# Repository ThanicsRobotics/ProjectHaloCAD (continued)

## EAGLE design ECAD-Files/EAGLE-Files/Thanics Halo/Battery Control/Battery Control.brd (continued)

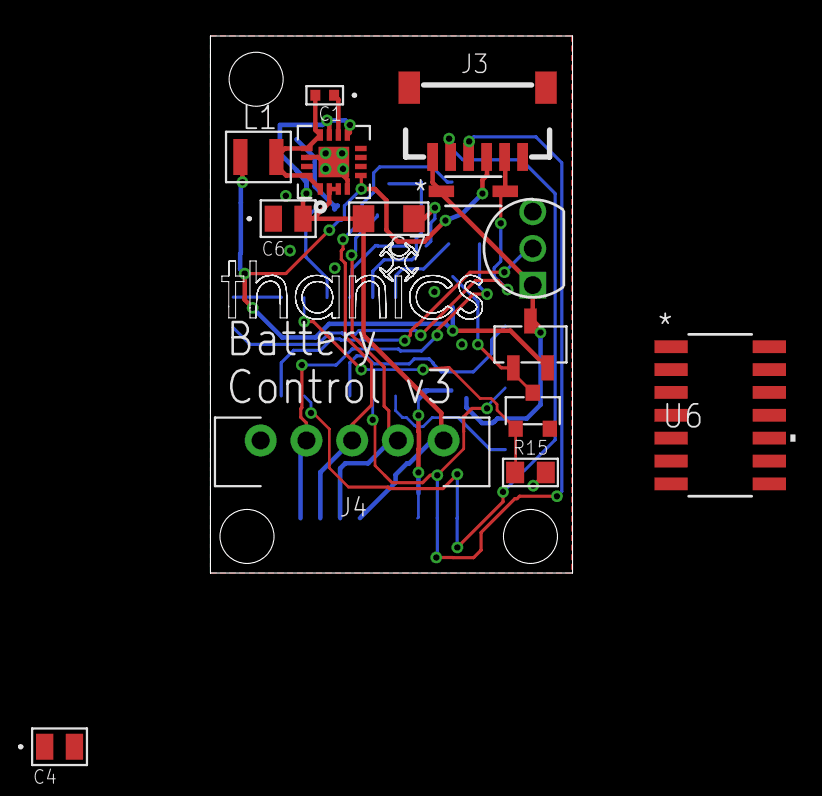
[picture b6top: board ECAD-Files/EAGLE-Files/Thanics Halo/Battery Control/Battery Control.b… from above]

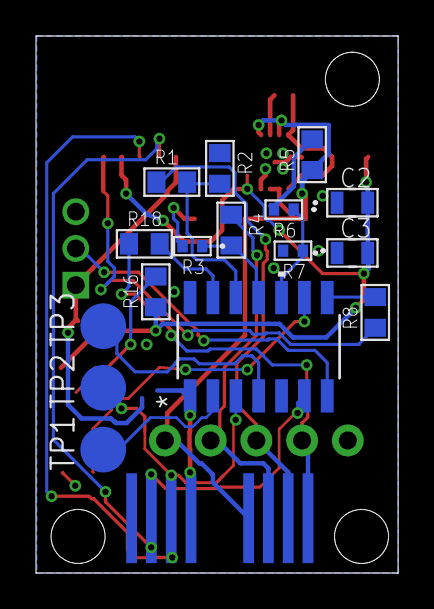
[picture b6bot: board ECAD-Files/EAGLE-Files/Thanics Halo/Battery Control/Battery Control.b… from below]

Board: 2 copper layers, 20.1 x 29.8 mm, 31 parts (17 on the bottom side), 23 nets.

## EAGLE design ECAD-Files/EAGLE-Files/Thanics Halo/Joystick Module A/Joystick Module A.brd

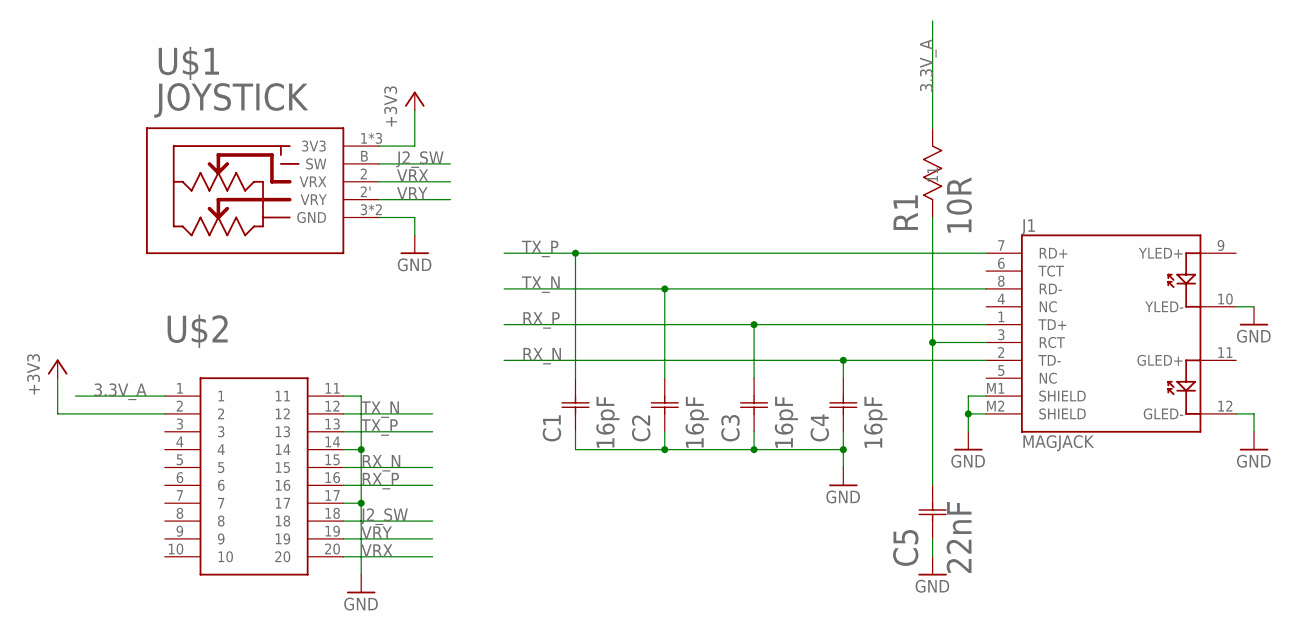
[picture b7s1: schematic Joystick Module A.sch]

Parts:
C1, C2, C3, C4: 16pF; G-155-M
C5: 22nF; G-155-M
J1: MAGJACK
R1: 10R; STA_RNCP0805-M
U$1: JOYSTICK"; JOYSTICK
U$2: EDGE_CONNECTOR_20POS_CONTACTS

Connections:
3.3V_A: R1.2 (22), U$2.1
+3V3: U$1.1 (3V3), U$1.1' (3V3), U$1.A (3V3), U$2.2
GND: C1.1 (11), C2.1 (11), C3.1 (11), C4.1 (11), C5.1 (11), J1.10 (YLED-), J1.12 (GLED-), J1.M1 (SHIELD), J1.M2 (SHIELD), U$1.3 (GND), U$1.3' (GND), U$2.11, U$2.14, U$2.17
J2_SW: U$1.B (SW), U$2.18
unnamed: C5.2 (22), J1.3 (RCT), R1.1 (11)
RX_N: C4.2 (22), J1.2 (TD-), U$2.15
RX_P: C3.2 (22), J1.1 (TD+), U$2.16
TX_N: C2.2 (22), J1.8 (RD-), U$2.12
TX_P: C1.2 (22), J1.7 (RD+), U$2.13
VRX: U$1.2 (VRX), U$2.20
VRY: U$1.2' (VRY), U$2.19

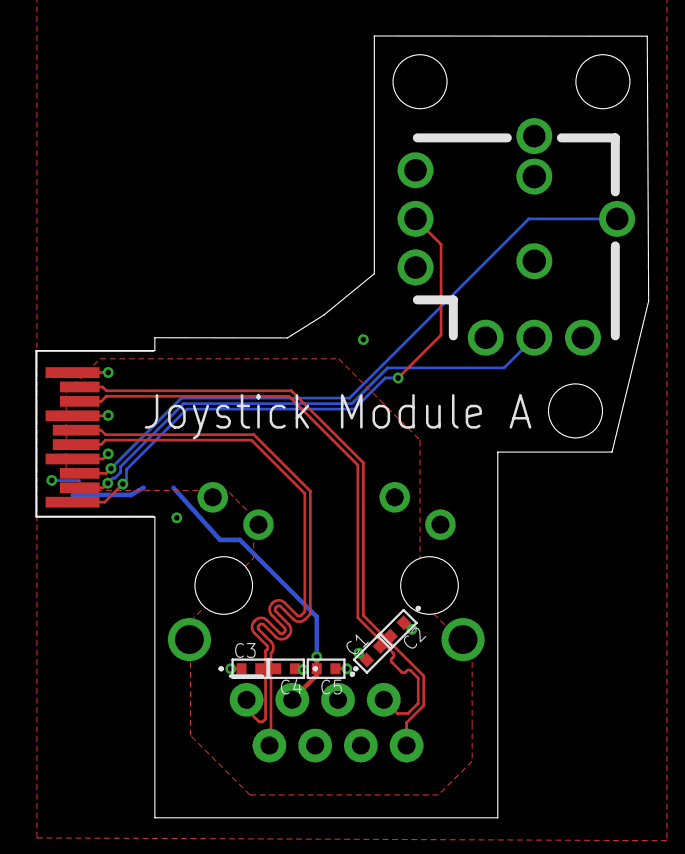
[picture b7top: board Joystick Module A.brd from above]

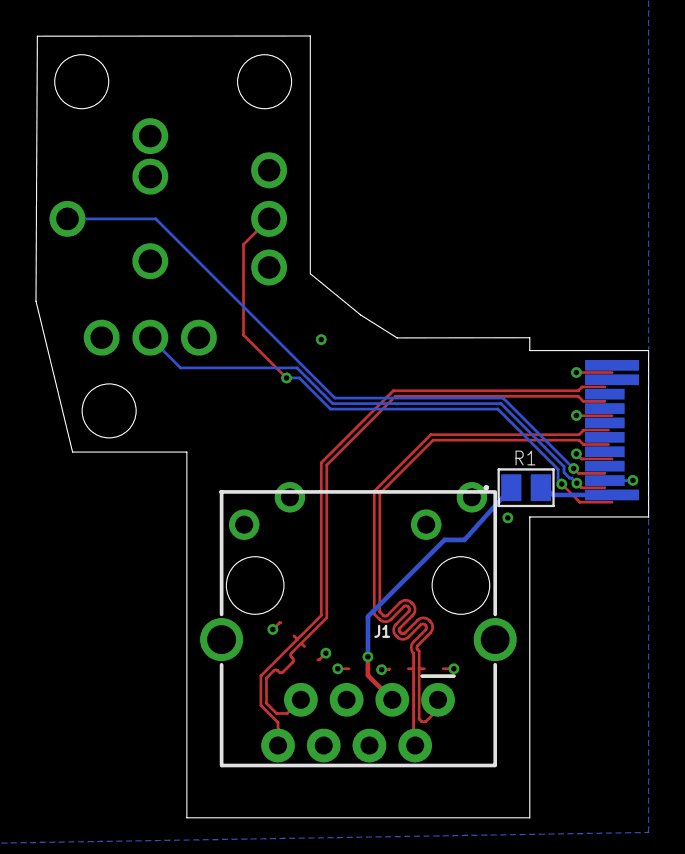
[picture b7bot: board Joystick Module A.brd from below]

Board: 4 copper layers, 34.0 x 43.4 mm, 9 parts (2 on the bottom side), 11 nets.

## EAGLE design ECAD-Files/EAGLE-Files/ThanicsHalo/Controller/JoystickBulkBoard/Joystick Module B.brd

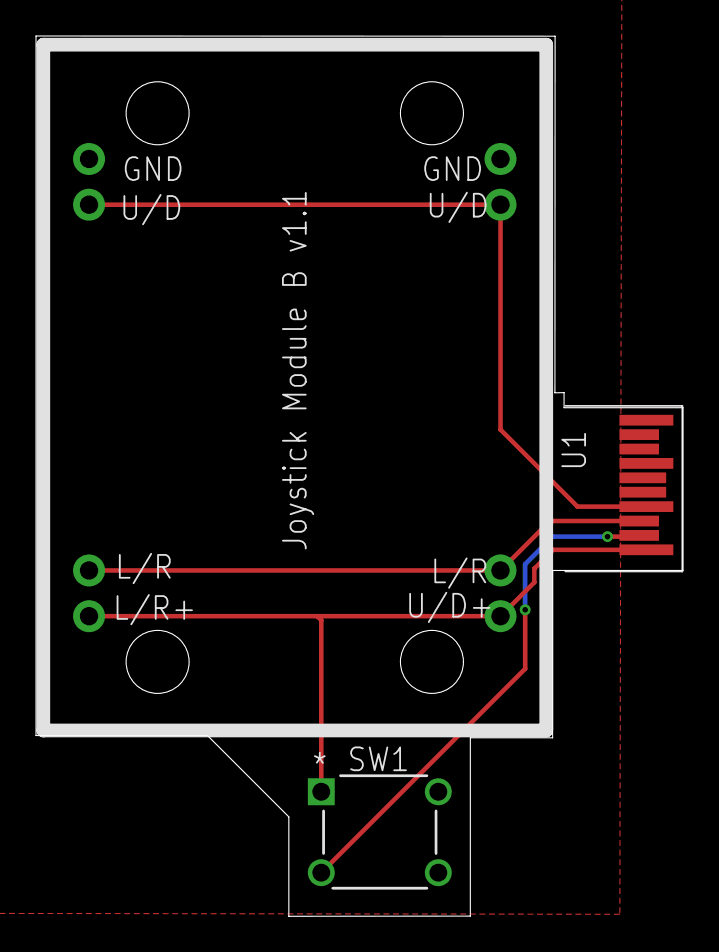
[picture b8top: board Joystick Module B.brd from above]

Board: 2 copper layers, 35.9 x 48.9 mm, 3 parts (0 on the bottom side), 5 nets.

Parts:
SW1: 2-1825910-7; SW4_1825910-G
U1: 27800-JOYSTICK
U$1: EDGE_CONNECTOR_20POS_CONTACTS

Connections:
+3V3: SW1.1, U1.1, U1.3, U$1.11
GND: U1.6, U1.8, U$1.15
J2_SW: SW1.3, U$1.12
VRX: U1.2, U1.4, U$1.13
VRY: U1.5, U1.7, U$1.14

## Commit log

2018-02-16 added mcad and ecad directories
2018-02-17 added block diagram directory
2018-02-17 added gitignore
2018-03-19 Started V3 Design
2018-03-22 Added Flight ESCs and power supply to PowerSwitchingBoard
2018-03-23 Added connectors
2018-03-23 Started routing programming traces
2018-03-23 Revert "Started routing programming traces"
    This reverts commit 430756d4e182701a37896144ea8eedb7b4574f9e.
2018-03-23 Revert "Revert "Started routing programming traces""
    This reverts commit ddc17bf72af711ebc9306e9f8ba822a91bb19f68.
2018-03-25 Fixed consistancy errors and finished routing
2018-03-27 Started Flight Controller Board Design
2018-03-28 Finished overall board zoning and component placement
2018-03-28 Repositioned ethernet pullup resistors
2018-03-30 Routed more traces, recognized that PowerSwitchingBoard connector needs to be reversed
2018-04-03 Finished Power Switching Board and Flight Controller Board v1
2018-04-04 Added Halo drone assembly archive file
2018-04-30 Changed ethernet capacitor isolation to transformers
2018-06-02 Created TOF Altimeter Board v1, and made power board 4 layers
2018-06-04 finished power board v1.2
2018-07-10 About to remove touchscreen from controller board
2018-07-12 Finished controller board v1.5
2018-07-26 Added new battery and joystick modules
2018-07-27 Changed folder name
2018-07-30 Fixed USB C connector sheild pin short problem
